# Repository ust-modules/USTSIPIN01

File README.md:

# USTSIPIN01B

It is intended for masurement of cosmic radiation and dosimetry by using Silicon PIN diode sensor.  

> USTSIPIN01B was originally named SPACEDOS01A_PCB01B

### Technical parameters

* Silicon PIN diode detector with 12.5 mm³ detection volume
* Number of energy channels 250
* Deposited energy range from 200 keV to 12 MeV
* Energy measurement resolution < 50 keV/channel
* Power supply 3.3 V / 3 mA
* Integration time 15 s
* Interface - RS232 TTL
* H x W  x  L - 15mm x 51mm x 91mm

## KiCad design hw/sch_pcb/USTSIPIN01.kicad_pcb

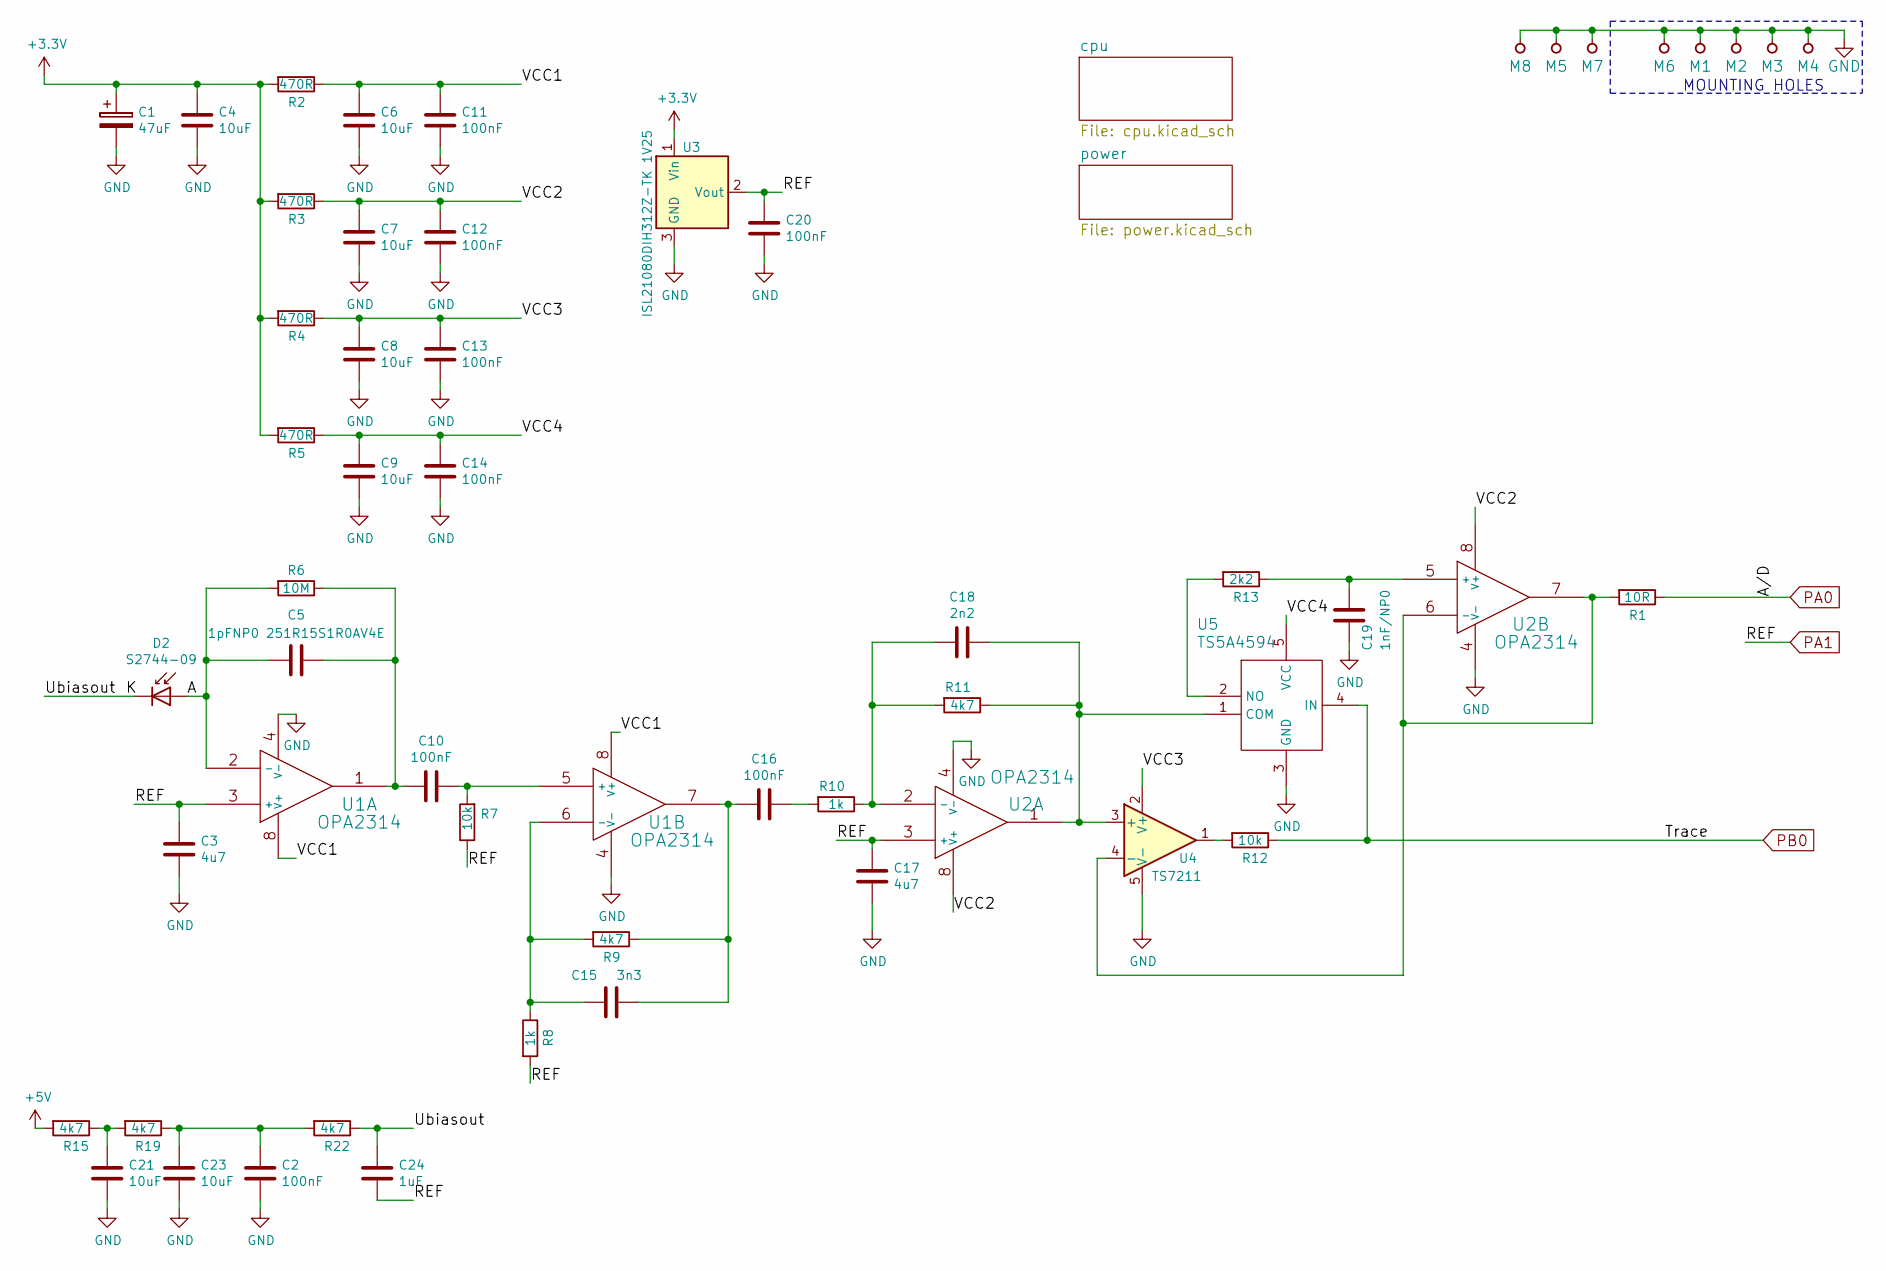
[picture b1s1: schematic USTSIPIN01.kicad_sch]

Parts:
C1: 47uF; TantalC_SizeC_Reflow
C2, C10, C11, C12, C13, C14, C16, C20: 100nF; SMD-0805
C3, C17: 4u7; SMD-0805
C4, C6, C7, C8, C9, C21, C23: 10uF; SMD-0805
C5: 1pFNP0 251R15S1R0AV4E; SMD-0805
C15: 3n3; SMD-0805
C18: 2n2; SMD-0805
C19: 1nF/NP0; SMD-0805
C24: 1uF; SMD-0805
D2: S2744-09; HAMAMATSU_S2744-09
M1, M2, M3, M4: HOLE; MountingHole_3mm
M5, M6, M7: BMI-S-210-F
M8: BMI-S-204-F; Laird_Technologies_BMI-S-204-F_32.00x32.00mm
R1: 10R; SMD-0805
R2, R3, R4, R5: 470R; SMD-0805
R6: 10M; SMD-0805
R7, R12: 10k; SMD-0805
R8, R10: 1k; SMD-0805
R9, R11, R15, R19, R22: 4k7; SMD-0805
R13: 2k2; SMD-0805
U1, U2: OPA2314; SOIC-8_3.9x4.9mm_Pitch1.27mm
U3: ISL21080DIH312Z-TK 1V25; SOT-23
U4: TS7211; SOT-23-5_HandSoldering
U5: TS5A4594; SOT-23-5_HandSoldering

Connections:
+3V3: C1.1, C4.1, R2.2, R3.2, R4.2, R5.2, U3.1 (Vin); also elsewhere on the board
+5V: R15.2; also elsewhere on the board
/A: C5.2, D2.2 (A), R6.2, U1.2 (-)
/K: C24.1, D2.1 (K), R22.1
/VCC1: C6.1, C11.1, R2.1, U1.8 (V+)
/VCC2: C7.1, C12.1, R3.1, U2.8 (V+)
/VCC3: C8.1, C13.1, R4.1, U4.2 (V+)
/VCC4: C9.1, C14.1, R5.1, U5.5 (VCC)
GND: C1.2, C2.2, C3.2, C4.2, C6.2, C7.2, C8.2, C9.2, C11.2, C12.2, C13.2, C14.2, C17.2, C19.2, C20.2, C21.2, C23.2, M1.1, M2.1, M3.1, M4.1, M5.1, M6.1, M7.1, M8.1, U1.4 (V-), U2.4 (V-), U3.3 (GND), U4.5 (V-), U5.3 (GND); also elsewhere on the board
unnamed: C2.1, C23.1, R19.1, R22.2
unnamed: C10.1, R7.2, U1.5 (+)
unnamed: C5.1, C10.2, R6.1, U1.1
unnamed: C15.1, C16.2, R9.1, U1.7
unnamed: C15.2, R8.1, R9.2, U1.6 (-)
unnamed: C16.1, R10.2
unnamed: C18.1, R11.1, U2.1, U4.3 (+), U5.1 (COM)
unnamed: C18.2, R10.1, R11.2, U2.2 (-)
unnamed: C19.1, R13.1, U2.5 (+)
unnamed: C21.1, R15.1, R19.2
unnamed: R1.2, U2.6 (-), U2.7, U4.4 (-)
unnamed: R12.2, U4.1
unnamed: R13.2, U5.2 (NO)
PA0: R1.1; also elsewhere on the board
PA1: C3.1, C17.1, C20.1, C24.2, R7.1, R8.2, U1.3 (+), U2.3 (+), U3.2 (Vout); also elsewhere on the board
PB0: R12.1, U5.4 (IN); also elsewhere on the board

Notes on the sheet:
MOUNTING HOLES

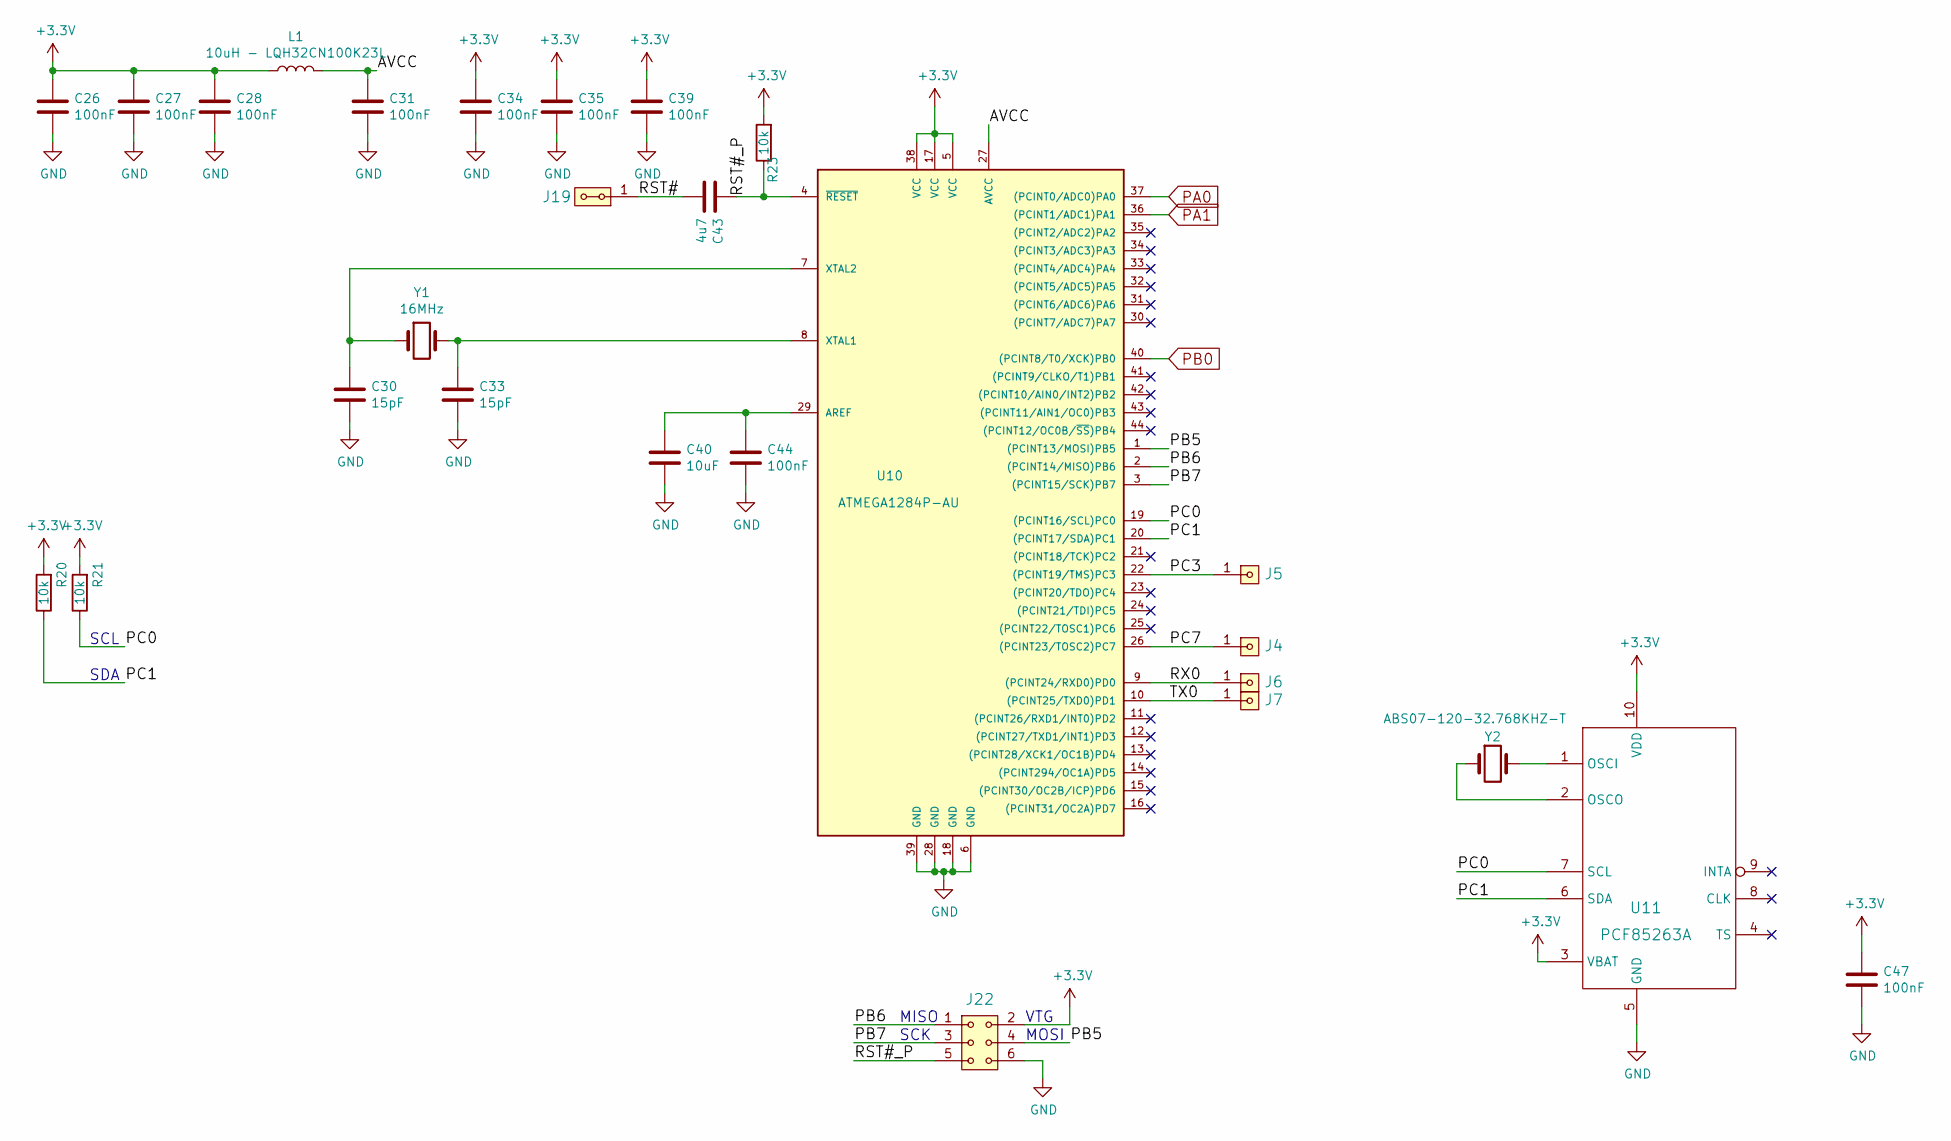
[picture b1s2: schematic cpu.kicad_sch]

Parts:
C26, C27, C28, C31, C34, C35, C39, C44, C47: 100nF; SMD-0805
C30, C33: 15pF; SMD-0805
C40: 10uF; SMD-0805
C43: 4u7; SMD-0805
J4, J5, J6, J7: HEADER_1x01; Straight_1x01
J19: HEADER_2x01_PARALLEL; Straight_2x01
J22: HEADER_2x03; SMD_2x03
L1: 10uH - LQH32CN100K23L; SMD-1210
R20, R21, R23: 10k; SMD-0805
U10: ATMEGA1284P-AU; TQFP-44_10x10mm_P0.8mm
U11: PCF85263A; TSSOP-10_3x3mm_Pitch0.5mm
Y1: 16MHz; Crystal_HC49-4H_Vertical
Y2: ABS07-120-32.768KHZ-T; ABS07

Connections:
+3V3: C26.1, C27.1, C28.1, C34.1, C35.1, C39.1, C47.1, J22.2, L1.1, R20.2, R21.2, R23.2, U10.5 (VCC), U10.17 (VCC), U10.38 (VCC), U11.3 (VBAT), U11.10 (VDD); also elsewhere on the board
/cpu/AVCC: C31.1, L1.2, U10.27 (AVCC)
/cpu/PB5: J22.4, U10.1 ((PCINT13/MOSI)PB5)
/cpu/PB6: J22.1, U10.2 ((PCINT14/MISO)PB6)
/cpu/PB7: J22.3, U10.3 ((PCINT15/SCK)PB7)
/cpu/PC0: R21.1, U10.19 ((PCINT16/SCL)PC0), U11.7 (SCL)
/cpu/PC1: R20.1, U10.20 ((PCINT17/SDA)PC1), U11.6 (SDA)
/cpu/PC3: J5.1, U10.22 ((PCINT19/TMS)PC3)
/cpu/PC7: J4.1, U10.26 ((PCINT23/TOSC2)PC7)
/cpu/RST#: C43.2, J19.1, J19.2
/cpu/RST#_P: C43.1, J22.5, R23.1, U10.4 (~RESET)
/cpu/RX0: J6.1, U10.9 ((PCINT24/RXD0)PD0)
/cpu/TX0: J7.1, U10.10 ((PCINT25/TXD0)PD1)
GND: C26.2, C27.2, C28.2, C30.2, C31.2, C33.2, C34.2, C35.2, C39.2, C40.2, C44.2, C47.2, J22.6, U10.6 (GND), U10.18 (GND), U10.28 (GND), U10.39 (GND), U11.5 (GND); also elsewhere on the board
unnamed: C30.1, U10.7 (XTAL2), Y1.1
unnamed: C33.1, U10.8 (XTAL1), Y1.2
unnamed: C40.1, C44.1, U10.29 (AREF)
unnamed: U11.1 (OSCI), Y2.2
unnamed: U11.2 (OSCO), Y2.1
PA0: U10.37 ((PCINT0/ADC0)PA0); also elsewhere on the board
PA1: U10.36 ((PCINT1/ADC1)PA1); also elsewhere on the board
PB0: U10.40 ((PCINT8/T0/XCK)PB0); also elsewhere on the board

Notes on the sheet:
MISO
MOSI
VTG
SCL
SCK
SDA

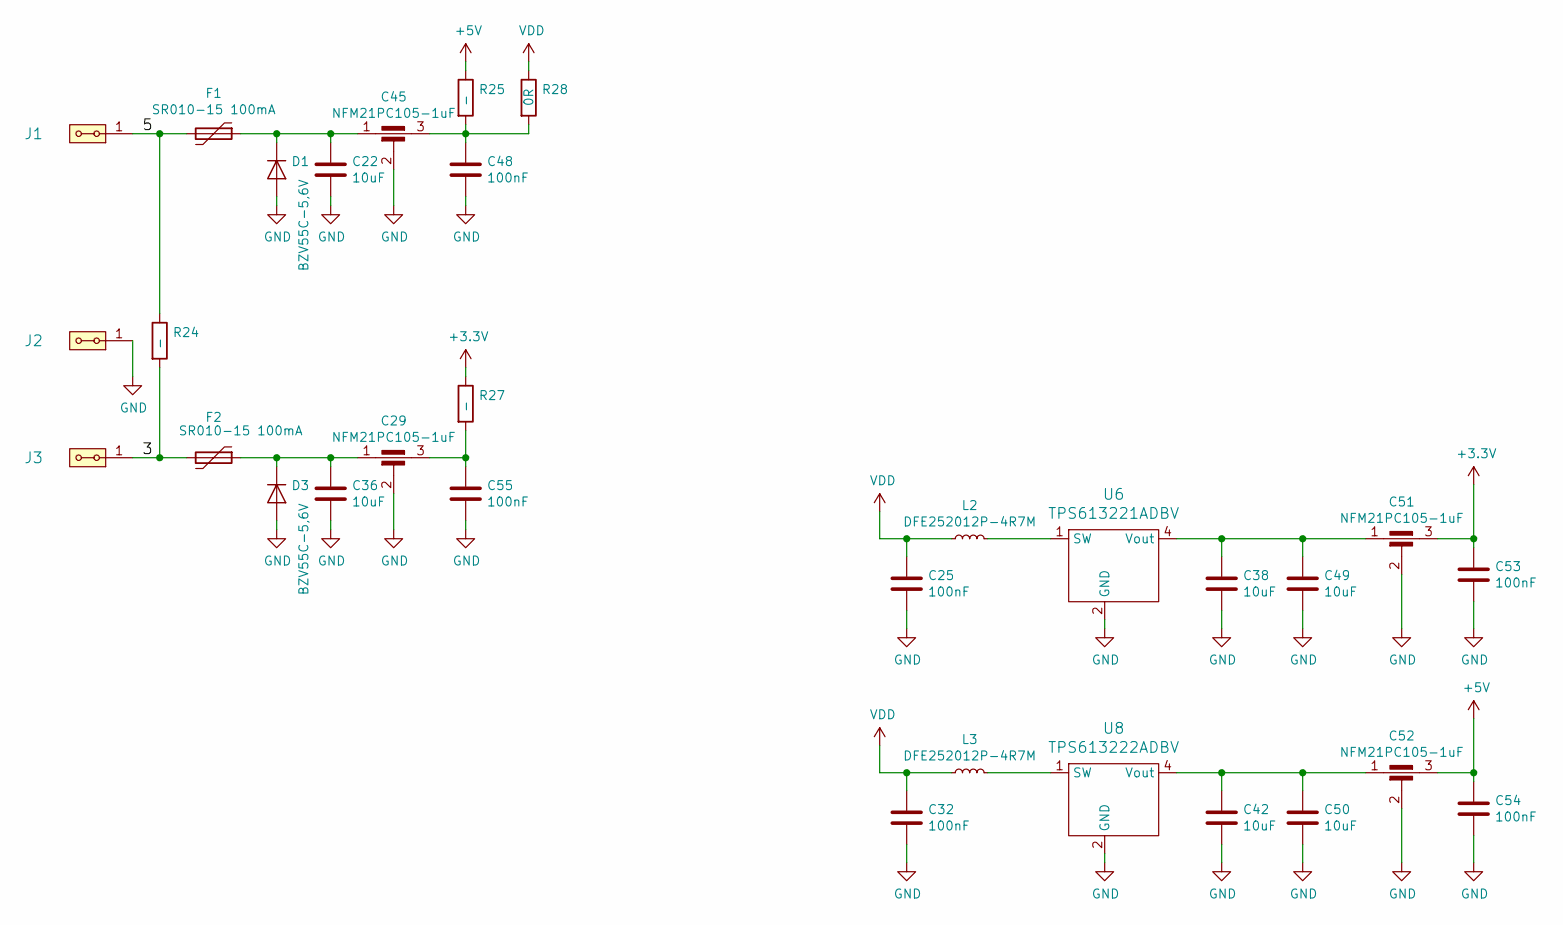
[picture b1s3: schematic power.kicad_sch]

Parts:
C22, C36, C38, C42, C49, C50: 10uF; SMD-0805
C25, C32, C48, C53, C54, C55: 100nF; SMD-0805
C29, C45, C51, C52: NFM21PC105-1uF; FIR1
D1, D3: BZV55C-5,6V; D_MiniMELF
F1, F2: SR010-15 100mA; SMD-0805
J1, J2, J3: HEADER_2x01_PARALLEL; Straight_1x02
L2, L3: DFE252012P-4R7M; R_0805_2012Metric_Pad1.15x1.40mm_HandSolder
R24, R25, R27: -; SMD-0805
R28: 0R; SMD-0805
U6: TPS613221ADBV; SOT-23-5
U8: TPS613222ADBV; SOT-23-5

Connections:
+3V3: C51.3, C53.1, R27.1; also elsewhere on the board
+5V: C52.3, C54.1, R25.1; also elsewhere on the board
/power/3: F2.2, J3.1, J3.2, R24.2
/power/5: F1.2, J1.1, J1.2, R24.1
GND: C22.2, C25.2, C29.2, C32.2, C36.2, C38.2, C42.2, C45.2, C48.2, C49.2, C50.2, C51.2, C52.2, C53.2, C54.2, C55.2, D1.2 (A), D3.2 (A), J2.1, J2.2, U6.2 (GND), U8.2 (GND); also elsewhere on the board
unnamed: C22.1, C45.1, D1.1 (K), F1.1
unnamed: C29.1, C36.1, D3.1 (K), F2.1
unnamed: C29.3, C55.1, R27.2
unnamed: C38.1, C49.1, C51.1, U6.4 (Vout)
unnamed: C42.1, C50.1, C52.1, U8.4 (Vout)
unnamed: C45.3, C48.1, R25.2, R28.2
unnamed: L2.2, U6.1 (SW)
unnamed: L3.2, U8.1 (SW)
VDD: C25.1, C32.1, L2.1, L3.1, R28.1

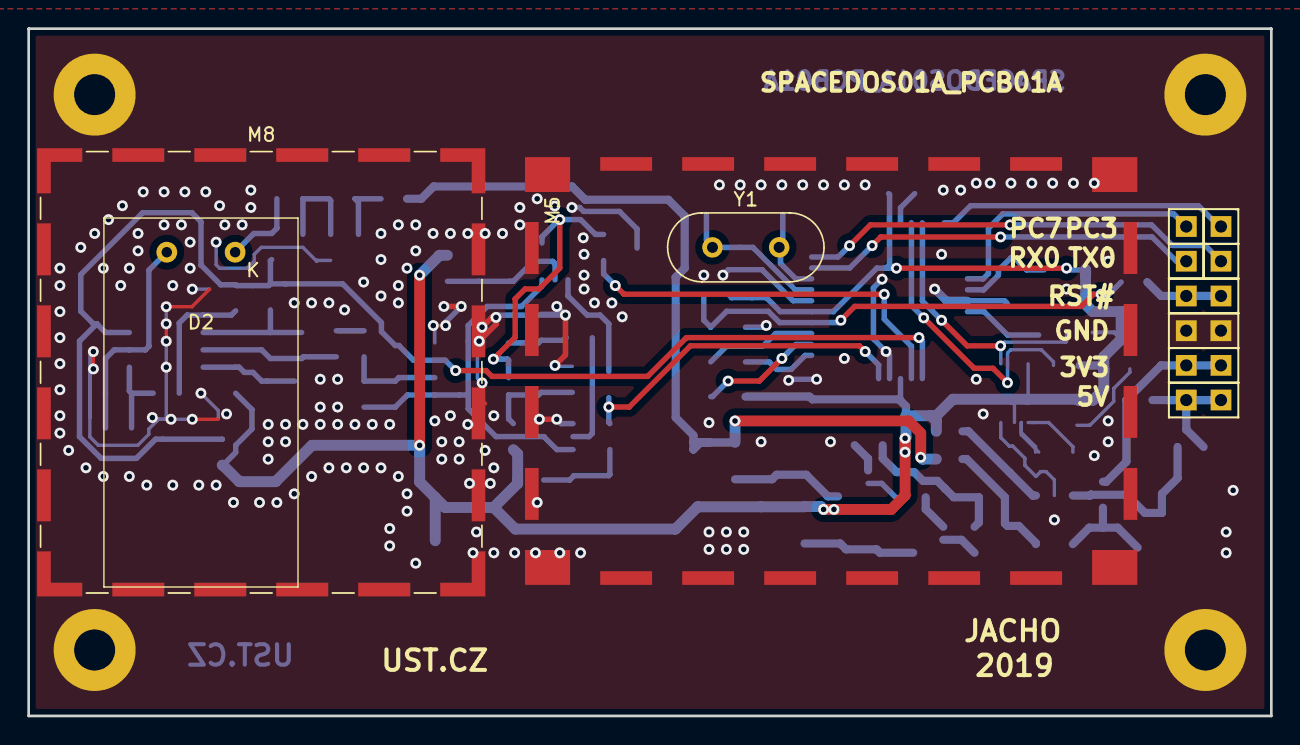
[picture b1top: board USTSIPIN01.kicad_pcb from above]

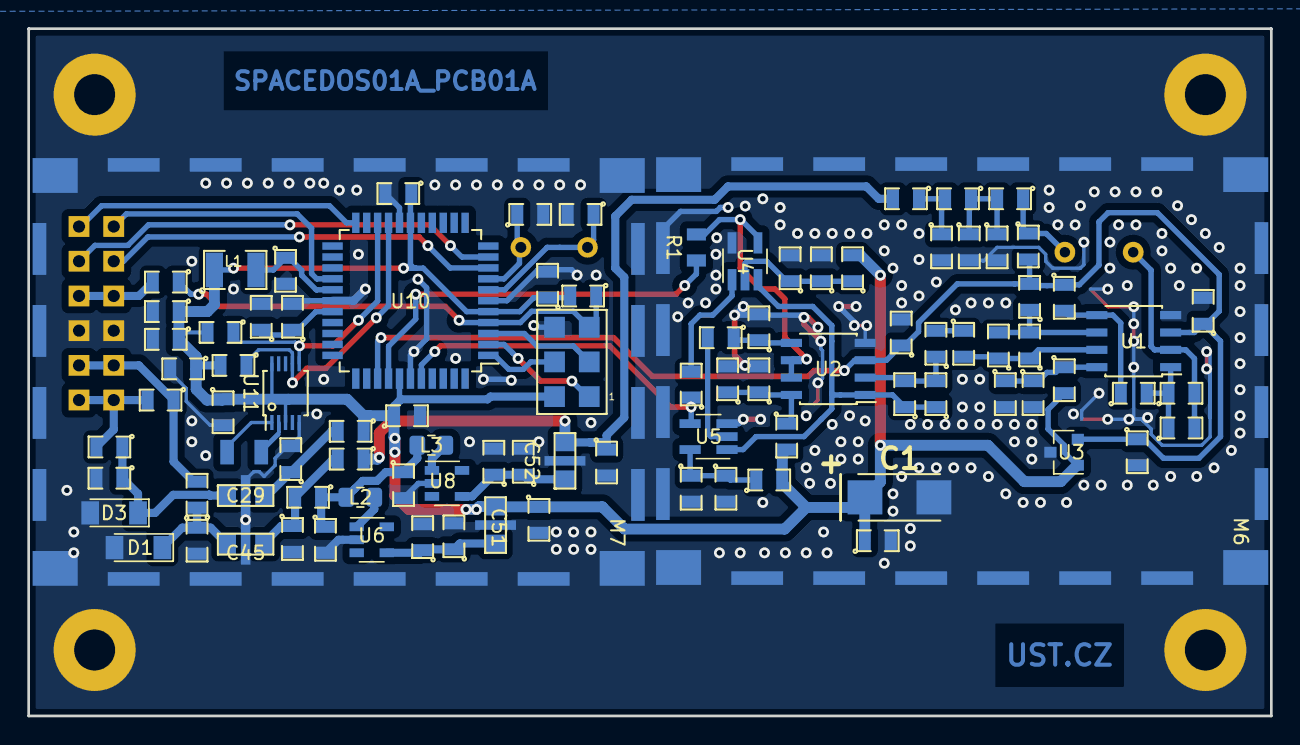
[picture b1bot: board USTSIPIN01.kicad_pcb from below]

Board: 2 copper layers, 90.9 x 50.3 mm, 111 parts (95 on the bottom side), 53 nets.

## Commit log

2022-04-16 Clean repository, become independent USTSIPIN01
2022-04-16 Update actions products
2022-04-18 Add o photo of "resetitko" testing setup.
